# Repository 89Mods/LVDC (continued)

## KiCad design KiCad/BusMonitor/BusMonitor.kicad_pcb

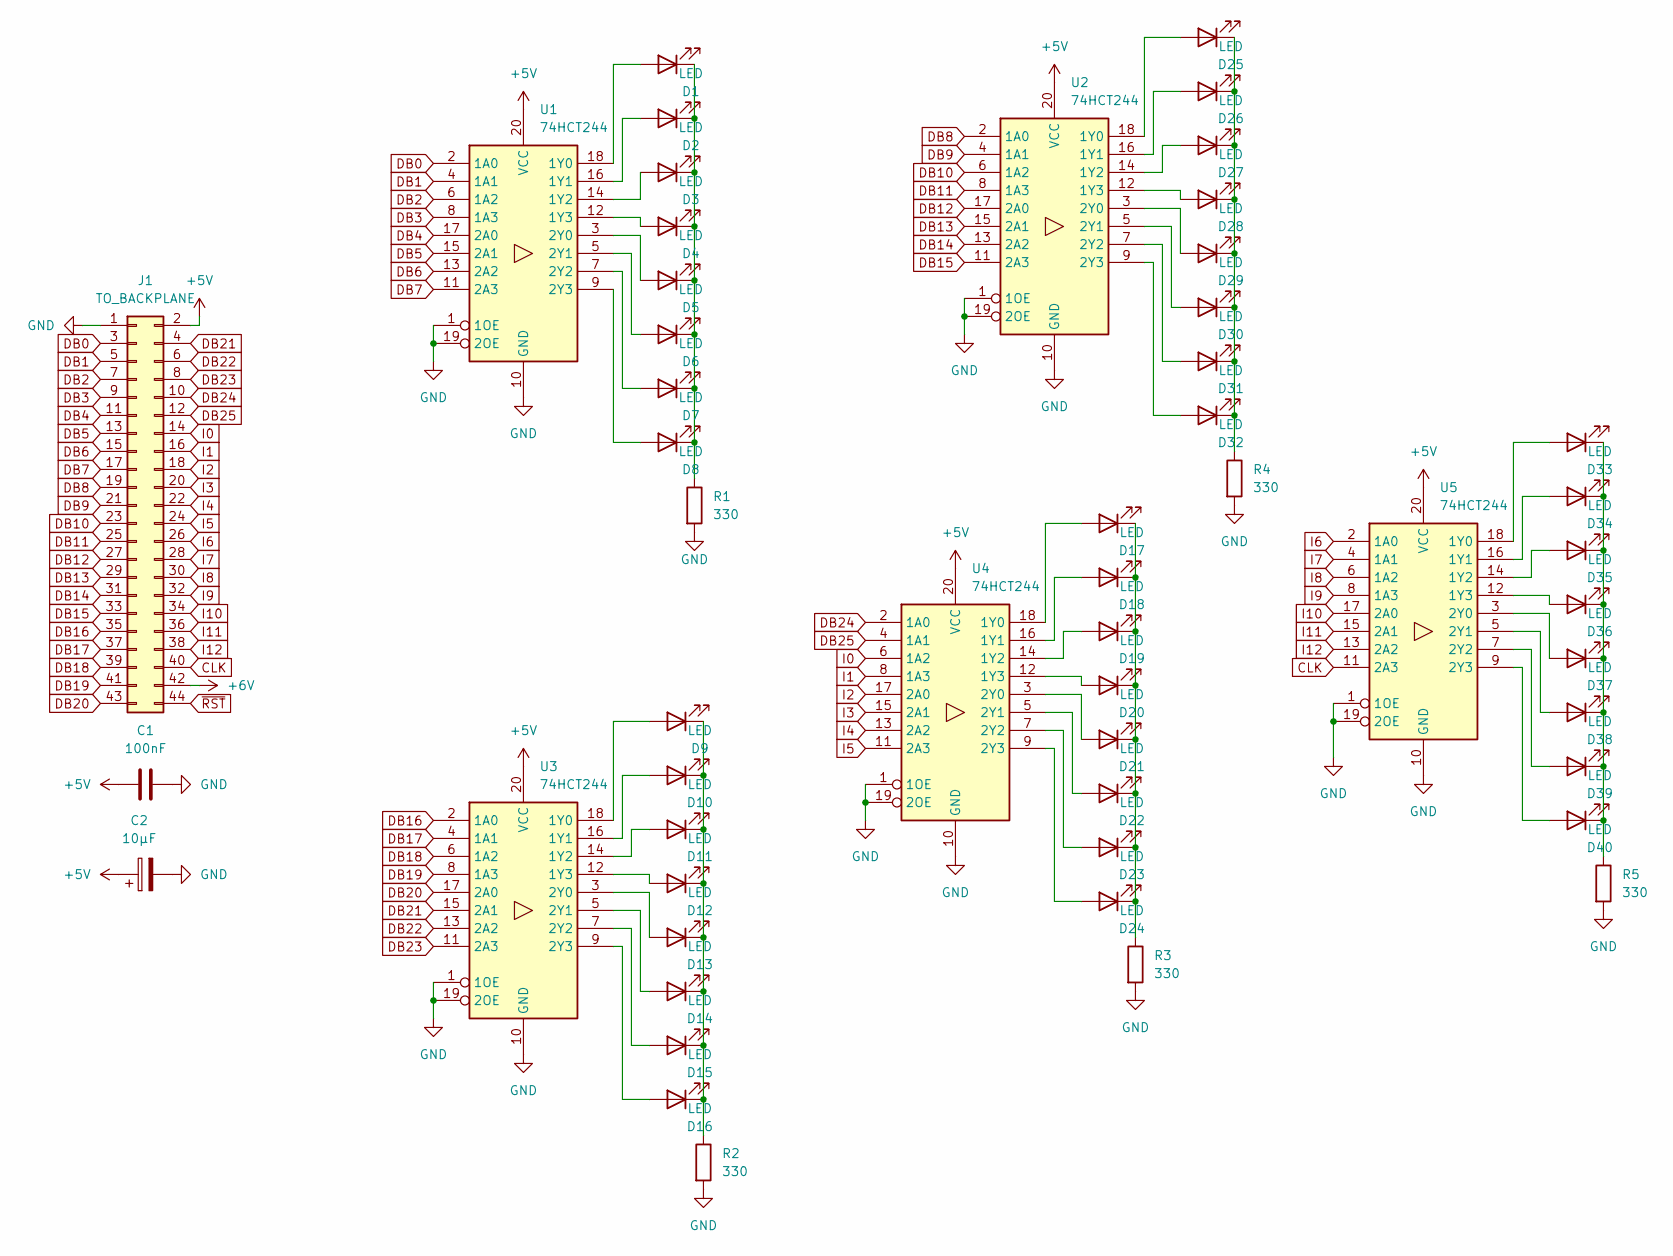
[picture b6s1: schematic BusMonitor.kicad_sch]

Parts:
C1: 100nF; C_0805_2012Metric_Pad1.18x1.45mm_HandSolder
C2: 10µF; CP_Radial_D4.0mm_P2.00mm
D1, D2, D3, D4, D5, D6, D7, D8, D9, D10, D11, D12, D13, D14, D15, D16, D17, D18, D19, D20, D21, D22, D23, D24, D25, D26, D27, D28, D29, D30, D31, D32, D33, D34, D35, D36, D37, D38, D39, D40: LED; LED_1206_3216Metric_Pad1.42x1.75mm_HandSolder
J1: TO_BACKPLANE; PinHeader_2x22_P2.54mm_Vertical
R1, R2, R3, R4, R5: 330; R_1206_3216Metric_Pad1.30x1.75mm_HandSolder
U1, U2, U3, U4, U5: 74HCT244; SO-20_12.8x7.5mm_P1.27mm

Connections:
+5V: C1.1, C2.1, J1.2, U1.20 (VCC), U2.20 (VCC), U3.20 (VCC), U4.20 (VCC), U5.20 (VCC)
+6V: J1.42
CLK: J1.40, U5.11 (2A3)
DB0: J1.3, U1.2 (1A0)
DB1: J1.5, U1.4 (1A1)
DB2: J1.7, U1.6 (1A2)
DB3: J1.9, U1.8 (1A3)
DB4: J1.11, U1.17 (2A0)
DB5: J1.13, U1.15 (2A1)
DB6: J1.15, U1.13 (2A2)
DB7: J1.17, U1.11 (2A3)
DB8: J1.19, U2.2 (1A0)
DB9: J1.21, U2.4 (1A1)
DB10: J1.23, U2.6 (1A2)
DB11: J1.25, U2.8 (1A3)
DB12: J1.27, U2.17 (2A0)
DB13: J1.29, U2.15 (2A1)
DB14: J1.31, U2.13 (2A2)
DB15: J1.33, U2.11 (2A3)
DB16: J1.35, U3.2 (1A0)
DB17: J1.37, U3.4 (1A1)
DB18: J1.39, U3.6 (1A2)
DB19: J1.41, U3.8 (1A3)
DB20: J1.43, U3.17 (2A0)
DB21: J1.4, U3.15 (2A1)
DB22: J1.6, U3.13 (2A2)
DB23: J1.8, U3.11 (2A3)
DB24: J1.10, U4.2 (1A0)
DB25: J1.12, U4.4 (1A1)
GND: C1.2, C2.2, J1.1, R1.2, R2.2, R3.2, R4.2, R5.2, U1.1 (1OE), U1.10 (GND), U1.19 (2OE), U2.1 (1OE), U2.10 (GND), U2.19 (2OE), U3.1 (1OE), U3.10 (GND), U3.19 (2OE), U4.1 (1OE), U4.10 (GND), U4.19 (2OE), U5.1 (1OE), U5.10 (GND), U5.19 (2OE)
I0: J1.14, U4.6 (1A2)
I1: J1.16, U4.8 (1A3)
I2: J1.18, U4.17 (2A0)
I3: J1.20, U4.15 (2A1)
I4: J1.22, U4.13 (2A2)
I5: J1.24, U4.11 (2A3)
I6: J1.26, U5.2 (1A0)
I7: J1.28, U5.4 (1A1)
I8: J1.30, U5.6 (1A2)
I9: J1.32, U5.8 (1A3)
I10: J1.34, U5.17 (2A0)
I11: J1.36, U5.15 (2A1)
I12: J1.38, U5.13 (2A2)
unnamed: D1.2 (A), U1.18 (1Y0)
unnamed: D1.1 (K), D2.1 (K), D3.1 (K), D4.1 (K), D5.1 (K), D6.1 (K), D7.1 (K), D8.1 (K), R1.1
unnamed: D2.2 (A), U1.16 (1Y1)
unnamed: D3.2 (A), U1.14 (1Y2)
unnamed: D4.2 (A), U1.12 (1Y3)
unnamed: D5.2 (A), U1.3 (2Y0)
unnamed: D6.2 (A), U1.5 (2Y1)
unnamed: D7.2 (A), U1.7 (2Y2)
unnamed: D8.2 (A), U1.9 (2Y3)
unnamed: D9.2 (A), U3.18 (1Y0)
unnamed: D10.2 (A), U3.16 (1Y1)
unnamed: D9.1 (K), D10.1 (K), D11.1 (K), D12.1 (K), D13.1 (K), D14.1 (K), D15.1 (K), D16.1 (K), R2.1
unnamed: D11.2 (A), U3.14 (1Y2)
unnamed: D12.2 (A), U3.12 (1Y3)
unnamed: D13.2 (A), U3.3 (2Y0)
unnamed: D14.2 (A), U3.5 (2Y1)
unnamed: D15.2 (A), U3.7 (2Y2)
unnamed: D16.2 (A), U3.9 (2Y3)
unnamed: D17.2 (A), U4.18 (1Y0)
unnamed: D17.1 (K), D18.1 (K), D19.1 (K), D20.1 (K), D21.1 (K), D22.1 (K), D23.1 (K), D24.1 (K), R3.1
unnamed: D18.2 (A), U4.16 (1Y1)
unnamed: D19.2 (A), U4.14 (1Y2)
unnamed: D20.2 (A), U4.12 (1Y3)
unnamed: D21.2 (A), U4.3 (2Y0)
unnamed: D22.2 (A), U4.5 (2Y1)
unnamed: D23.2 (A), U4.7 (2Y2)
unnamed: D24.2 (A), U4.9 (2Y3)
unnamed: D25.2 (A), U2.18 (1Y0)
unnamed: D25.1 (K), D26.1 (K), D27.1 (K), D28.1 (K), D29.1 (K), D30.1 (K), D31.1 (K), D32.1 (K), R4.1
unnamed: D26.2 (A), U2.16 (1Y1)
unnamed: D27.2 (A), U2.14 (1Y2)
unnamed: D28.2 (A), U2.12 (1Y3)
unnamed: D29.2 (A), U2.3 (2Y0)
unnamed: D30.2 (A), U2.5 (2Y1)
unnamed: D31.2 (A), U2.7 (2Y2)
unnamed: D32.2 (A), U2.9 (2Y3)
unnamed: D33.2 (A), U5.18 (1Y0)
unnamed: D33.1 (K), D34.1 (K), D35.1 (K), D36.1 (K), D37.1 (K), D38.1 (K), D39.1 (K), D40.1 (K), R5.1
unnamed: D34.2 (A), U5.16 (1Y1)
unnamed: D35.2 (A), U5.14 (1Y2)
unnamed: D36.2 (A), U5.12 (1Y3)
unnamed: D37.2 (A), U5.3 (2Y0)
unnamed: D38.2 (A), U5.5 (2Y1)
unnamed: D39.2 (A), U5.7 (2Y2)
unnamed: D40.2 (A), U5.9 (2Y3)
~RST: J1.44

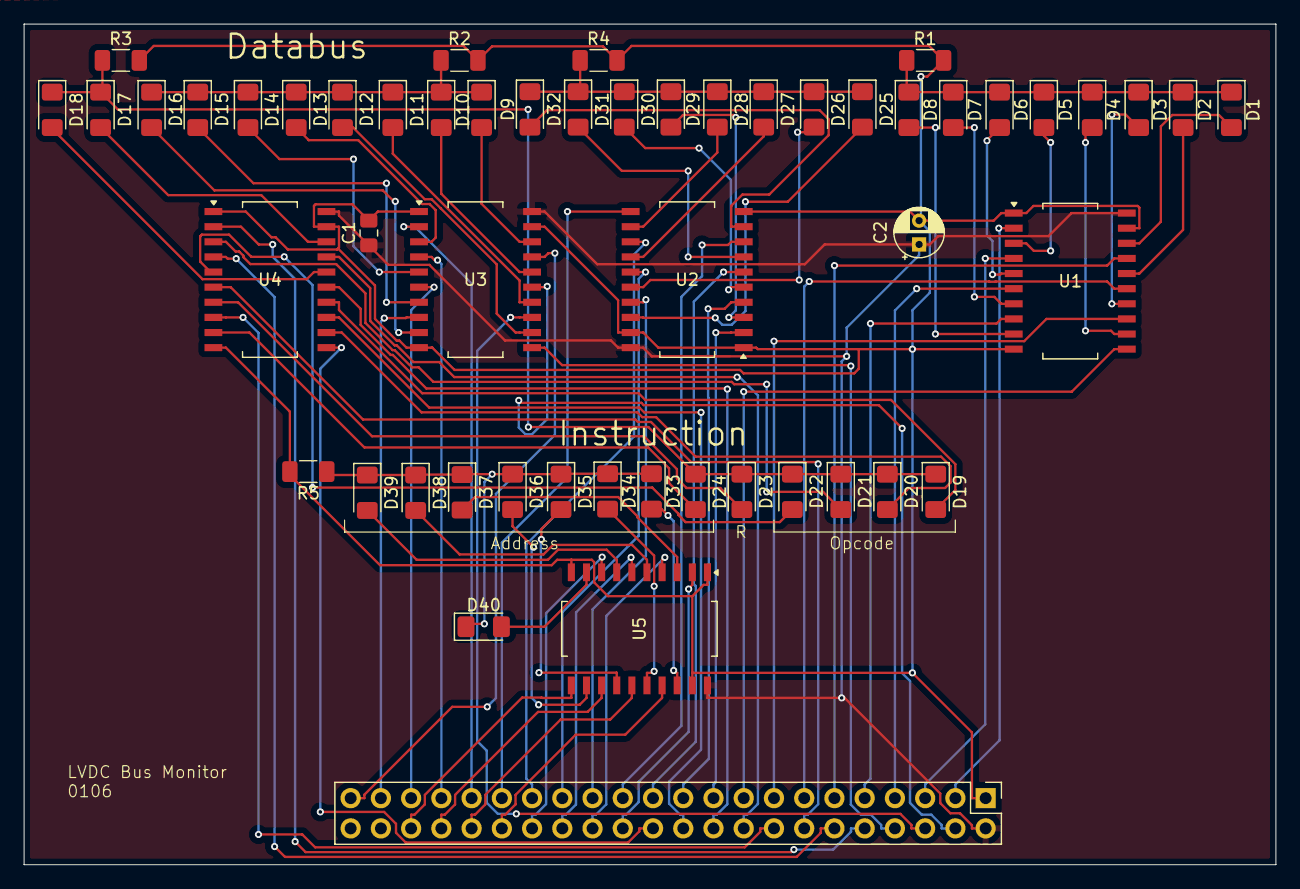
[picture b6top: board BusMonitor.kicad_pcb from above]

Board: 2 copper layers, 105.2 x 70.6 mm, 53 parts (0 on the bottom side), 87 nets.

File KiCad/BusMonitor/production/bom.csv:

Designator,Footprint,Quantity,Value,LCSC Part #
C1,0805,1,100nF,
C2,CP_Radial_D4.0mm_P2.00mm,1,10µF,
"D1, D10, D11, D12, D13, D14, D15, D16, D17, D18, D19, D2, D20, D21, D22, D23, D24, D25, D26, D27, D28, D29, D3, D30, D31, D32, D33, D34, D35, D36, D37, D38, D39, D4, D40, D5, D6, D7, D8, D9",1206,40,LED,
J1,PinHeader_2x22_P2.54mm_Vertical,1,TO_BACKPLANE,
"R1, R2, R3, R4, R5",1206,5,330,
"U1, U2, U3, U4, U5",SO-20_12.8x7.5mm_P1.27mm,5,74HCT244,

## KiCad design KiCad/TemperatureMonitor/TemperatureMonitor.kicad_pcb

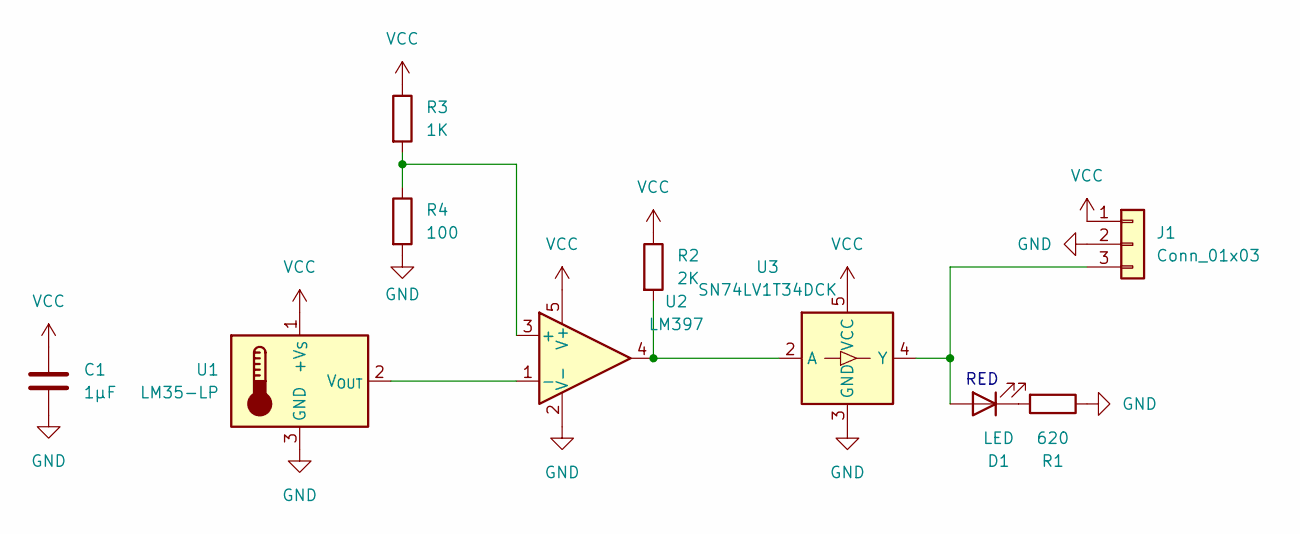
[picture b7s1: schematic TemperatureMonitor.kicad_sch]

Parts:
C1: 1µF; C_0805_2012Metric_Pad1.18x1.45mm_HandSolder
D1: LED; LED_1206_3216Metric_Pad1.42x1.75mm_HandSolder
J1: Conn_01x03; PinHeader_1x03_P2.54mm_Vertical
R1: 620; R_1206_3216Metric_Pad1.30x1.75mm_HandSolder
R2: 2K; R_1206_3216Metric_Pad1.30x1.75mm_HandSolder
R3: 1K; R_1206_3216Metric_Pad1.30x1.75mm_HandSolder
R4: 100; R_1206_3216Metric_Pad1.30x1.75mm_HandSolder
U1: LM35-LP; TO-92_Inline
U2: LM397; SOT-23-5
U3: SN74LV1T34DCK; SOT-23-5

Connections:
GND: C1.1, J1.2, R1.1, R4.2, U1.3 (GND), U2.2 (V-), U3.3 (GND)
unnamed: D1.2 (A), J1.3, U3.4 (Y)
unnamed: D1.1 (K), R1.2
unnamed: U1.2 (V_{OUT}), U2.1 (-)
unnamed: R3.2, R4.1, U2.3 (+)
unnamed: R2.2, U2.4, U3.2 (A)
VCC: C1.2, J1.1, R2.1, R3.1, U1.1 (+V_{S}), U2.5 (V+), U3.5 (VCC)

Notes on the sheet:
RED

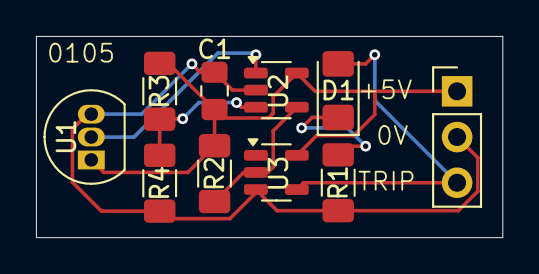
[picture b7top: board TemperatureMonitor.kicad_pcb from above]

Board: 2 copper layers, 25.9 x 11.2 mm, 10 parts (0 on the bottom side), 7 nets.

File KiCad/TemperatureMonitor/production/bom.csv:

Designator,Footprint,Quantity,Value,LCSC Part #
C1,0805,1,1µF,
D1,1206,1,LED,
J1,PinHeader_1x03_P2.54mm_Vertical,1,Conn_01x03,
R1,1206,1,620,
R2,1206,1,2K,
R3,1206,1,1K,
R4,1206,1,4.7K,
U1,TO-92_Inline,1,LM35-LP,
U2,SOT-23-5,1,LM397,
U3,SOT-23-5,1,SN74LV1T34DCK,

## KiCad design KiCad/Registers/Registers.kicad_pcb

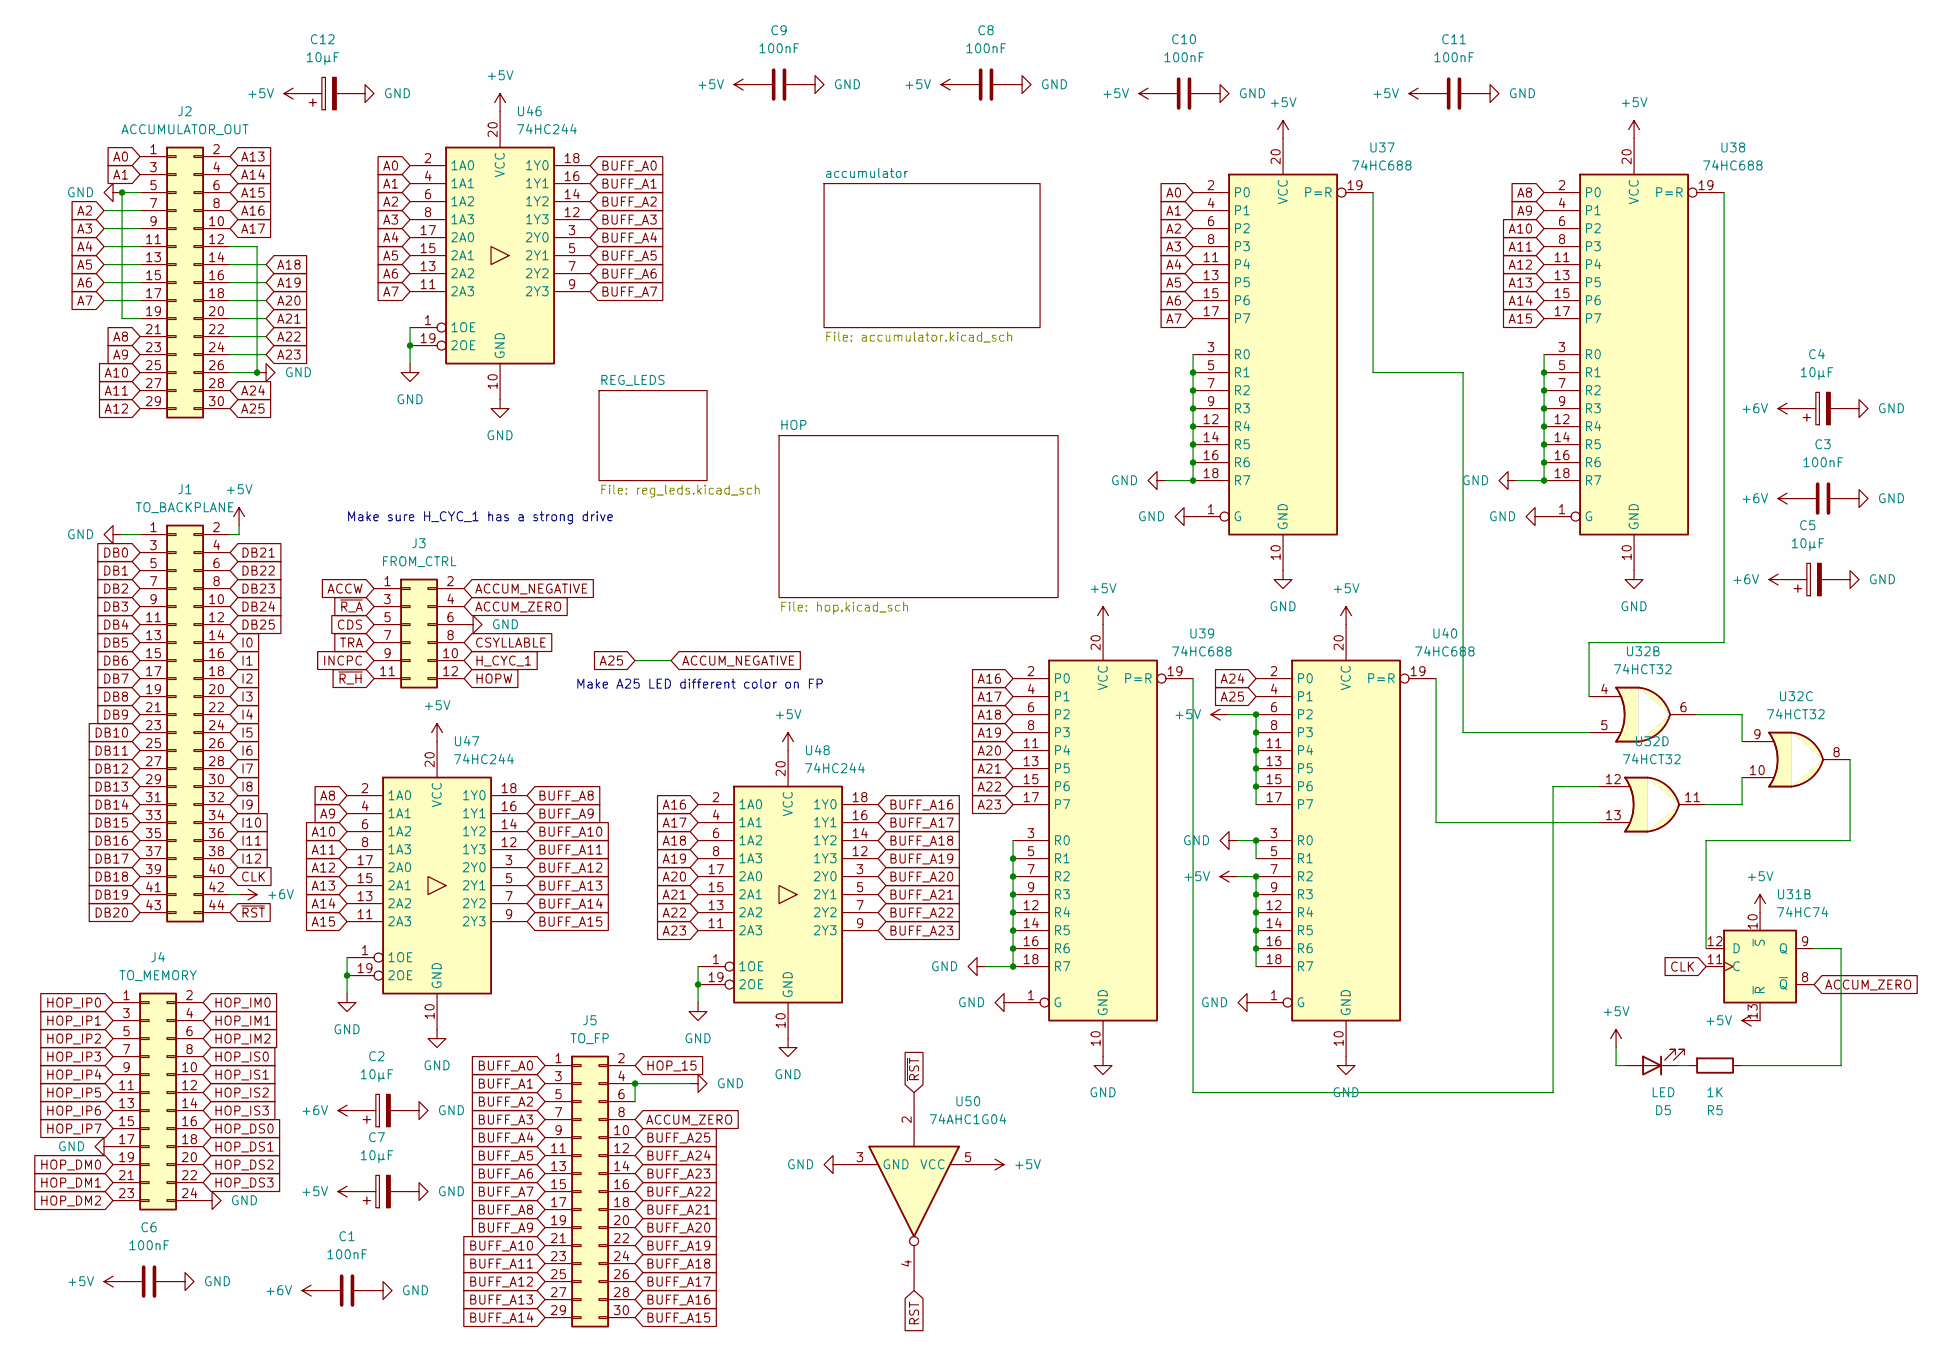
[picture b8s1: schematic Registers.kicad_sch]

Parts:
C1, C3, C6, C8, C9, C10, C11: 100nF; C_0805_2012Metric_Pad1.18x1.45mm_HandSolder
C2, C4, C5, C7, C12: 10µF; CP_Radial_D4.0mm_P2.00mm
D5: LED; LED_1206_3216Metric_Pad1.42x1.75mm_HandSolder
J1: TO_BACKPLANE; PinHeader_2x22_P2.54mm_Vertical
J2: ACCUMULATOR_OUT; PinHeader_2x15_P2.54mm_Vertical
J3: FROM_CTRL; PinHeader_2x06_P2.54mm_Vertical
J4: TO_MEMORY; PinHeader_2x12_P2.54mm_Vertical
J5: TO_FP; PinHeader_2x15_P2.54mm_Vertical
R5: 1K; R_1206_3216Metric_Pad1.30x1.75mm_HandSolder
U31: 74HC74; SO-14_3.9x8.65mm_P1.27mm
U32: 74HCT32; SO-14_3.9x8.65mm_P1.27mm
U37, U38, U39, U40: 74HC688; SO-20_12.8x7.5mm_P1.27mm
U46, U47, U48: 74HC244; SO-20_12.8x7.5mm_P1.27mm
U50: 74AHC1G04; SOIC-6

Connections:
+5V: C6.1, C7.1, C8.1, C9.1, C10.1, C11.1, C12.1, D5.2 (A), J1.2, U31.10 (~S), U31.13 (~R), U37.20 (VCC), U38.20 (VCC), U39.20 (VCC), U40.6 (P2), U40.7 (R2), U40.8 (P3), U40.9 (R3), U40.11 (P4), U40.12 (R4), U40.13 (P5), U40.14 (R5), U40.15 (P6), U40.16 (R6), U40.17 (P7), U40.18 (R7), U40.20 (VCC), U46.20 (VCC), U47.20 (VCC), U48.20 (VCC), U50.5 (VCC); also elsewhere on the board
+6V: C1.1, C2.1, C3.1, C4.1, C5.1, J1.42; also elsewhere on the board
A0: J2.1, U37.2 (P0), U46.2 (1A0); also elsewhere on the board
A1: J2.3, U37.4 (P1), U46.4 (1A1); also elsewhere on the board
A2: J2.7, U37.6 (P2), U46.6 (1A2); also elsewhere on the board
A3: J2.9, U37.8 (P3), U46.8 (1A3); also elsewhere on the board
A4: J2.11, U37.11 (P4), U46.17 (2A0); also elsewhere on the board
A5: J2.13, U37.13 (P5), U46.15 (2A1); also elsewhere on the board
A6: J2.15, U37.15 (P6), U46.13 (2A2); also elsewhere on the board
A7: J2.17, U37.17 (P7), U46.11 (2A3); also elsewhere on the board
A8: J2.21, U38.2 (P0), U47.2 (1A0); also elsewhere on the board
A9: J2.23, U38.4 (P1), U47.4 (1A1); also elsewhere on the board
A10: J2.25, U38.6 (P2), U47.6 (1A2); also elsewhere on the board
A11: J2.27, U38.8 (P3), U47.8 (1A3); also elsewhere on the board
A12: J2.29, U38.11 (P4), U47.17 (2A0); also elsewhere on the board
A13: J2.2, U38.13 (P5), U47.15 (2A1); also elsewhere on the board
A14: J2.4, U38.15 (P6), U47.13 (2A2); also elsewhere on the board
A15: J2.6, U38.17 (P7), U47.11 (2A3); also elsewhere on the board
A16: J2.8, U39.2 (P0), U48.2 (1A0); also elsewhere on the board
A17: J2.10, U39.4 (P1), U48.4 (1A1); also elsewhere on the board
A18: J2.14, U39.6 (P2), U48.6 (1A2); also elsewhere on the board
A19: J2.16, U39.8 (P3), U48.8 (1A3); also elsewhere on the board
A20: J2.18, U39.11 (P4), U48.17 (2A0); also elsewhere on the board
A21: J2.20, U39.13 (P5), U48.15 (2A1); also elsewhere on the board
A22: J2.22, U39.15 (P6), U48.13 (2A2); also elsewhere on the board
A23: J2.24, U39.17 (P7), U48.11 (2A3); also elsewhere on the board
A24: J2.28, U40.2 (P0); also elsewhere on the board
A25: J2.30, J3.2, U40.4 (P1); also elsewhere on the board
ACCUM_ZERO: J3.4, J5.8, U31.8 (~Q)
ACCW: J3.1; also elsewhere on the board
BUFF_A0: J5.1, U46.18 (1Y0)
BUFF_A1: J5.3, U46.16 (1Y1)
BUFF_A2: J5.5, U46.14 (1Y2)
BUFF_A3: J5.7, U46.12 (1Y3)
BUFF_A4: J5.9, U46.3 (2Y0)
BUFF_A5: J5.11, U46.5 (2Y1)
BUFF_A6: J5.13, U46.7 (2Y2)
BUFF_A7: J5.15, U46.9 (2Y3)
BUFF_A8: J5.17, U47.18 (1Y0)
BUFF_A9: J5.19, U47.16 (1Y1)
BUFF_A10: J5.21, U47.14 (1Y2)
BUFF_A11: J5.23, U47.12 (1Y3)
BUFF_A12: J5.25, U47.3 (2Y0)
BUFF_A13: J5.27, U47.5 (2Y1)
BUFF_A14: J5.29, U47.7 (2Y2)
BUFF_A15: J5.30, U47.9 (2Y3)
BUFF_A16: J5.28, U48.18 (1Y0)
BUFF_A17: J5.26, U48.16 (1Y1)
BUFF_A18: J5.24, U48.14 (1Y2)
BUFF_A19: J5.22, U48.12 (1Y3)
BUFF_A20: J5.20, U48.3 (2Y0)
BUFF_A21: J5.18, U48.5 (2Y1)
BUFF_A22: J5.16, U48.7 (2Y2)
BUFF_A23: J5.14, U48.9 (2Y3)
BUFF_A24: J5.12; also elsewhere on the board
BUFF_A25: J5.10; also elsewhere on the board
CDS: J3.5; also elsewhere on the board
CLK: J1.40, U31.11 (C); also elsewhere on the board
CSYLLABLE: J3.8; also elsewhere on the board
DB0: J1.3; also elsewhere on the board
DB1: J1.5; also elsewhere on the board
DB2: J1.7; also elsewhere on the board
DB3: J1.9; also elsewhere on the board
DB4: J1.11; also elsewhere on the board
DB5: J1.13; also elsewhere on the board
DB6: J1.15; also elsewhere on the board
DB7: J1.17; also elsewhere on the board
DB8: J1.19; also elsewhere on the board
DB9: J1.21; also elsewhere on the board
DB10: J1.23; also elsewhere on the board
DB11: J1.25; also elsewhere on the board
DB12: J1.27; also elsewhere on the board
DB13: J1.29; also elsewhere on the board
DB14: J1.31; also elsewhere on the board
DB15: J1.33; also elsewhere on the board
DB16: J1.35; also elsewhere on the board
DB17: J1.37; also elsewhere on the board
DB18: J1.39; also elsewhere on the board
DB19: J1.41; also elsewhere on the board
DB20: J1.43; also elsewhere on the board
DB21: J1.4; also elsewhere on the board
DB22: J1.6; also elsewhere on the board
DB23: J1.8; also elsewhere on the board
DB24: J1.10; also elsewhere on the board
DB25: J1.12; also elsewhere on the board
GND: C1.2, C2.2, C3.2, C4.2, C5.2, C6.2, C7.2, C8.2, C9.2, C10.2, C11.2, C12.2, J1.1, J2.5, J2.12, J2.19, J2.26, J3.6, J4.17, J4.24, J5.4, J5.6, U37.1 (G), U37.3 (R0), U37.5 (R1), U37.7 (R2), U37.9 (R3), U37.10 (GND), U37.12 (R4), U37.14 (R5), U37.16 (R6), U37.18 (R7), U38.1 (G), U38.3 (R0), U38.5 (R1), U38.7 (R2), U38.9 (R3), U38.10 (GND), U38.12 (R4), U38.14 (R5), U38.16 (R6), U38.18 (R7), U39.1 (G), U39.3 (R0), U39.5 (R1), U39.7 (R2), U39.9 (R3), U39.10 (GND), U39.12 (R4), U39.14 (R5), U39.16 (R6), U39.18 (R7), U40.1 (G), U40.3 (R0), U40.5 (R1), U40.10 (GND), U46.1 (1OE), U46.10 (GND), U46.19 (2OE), U47.1 (1OE), U47.10 (GND), U47.19 (2OE), U48.1 (1OE), U48.10 (GND), U48.19 (2OE), U50.3 (GND); also elsewhere on the board
HOPW: J3.12; also elsewhere on the board
HOP_15: J5.2; also elsewhere on the board
HOP_DM0: J4.19; also elsewhere on the board
HOP_DM1: J4.21; also elsewhere on the board
HOP_DM2: J4.23; also elsewhere on the board
HOP_DS0: J4.16; also elsewhere on the board
HOP_DS1: J4.18; also elsewhere on the board
HOP_DS2: J4.20; also elsewhere on the board
HOP_DS3: J4.22; also elsewhere on the board
HOP_IM0: J4.2; also elsewhere on the board
HOP_IM1: J4.4; also elsewhere on the board
HOP_IM2: J4.6; also elsewhere on the board
HOP_IP0: J4.1; also elsewhere on the board
HOP_IP1: J4.3; also elsewhere on the board
HOP_IP2: J4.5; also elsewhere on the board
HOP_IP3: J4.7; also elsewhere on the board
HOP_IP4: J4.9; also elsewhere on the board
HOP_IP5: J4.11; also elsewhere on the board
HOP_IP6: J4.13; also elsewhere on the board
HOP_IP7: J4.15; also elsewhere on the board
HOP_IS0: J4.8; also elsewhere on the board
HOP_IS1: J4.10; also elsewhere on the board
HOP_IS2: J4.12; also elsewhere on the board
HOP_IS3: J4.14; also elsewhere on the board
H_CYC_1: J3.10; also elsewhere on the board
I0: J1.14
I1: J1.16
I2: J1.18
I3: J1.20
I4: J1.22; also elsewhere on the board
I5: J1.24; also elsewhere on the board
I6: J1.26; also elsewhere on the board
I7: J1.28; also elsewhere on the board
I8: J1.30; also elsewhere on the board
I9: J1.32; also elsewhere on the board
I10: J1.34; also elsewhere on the board
I11: J1.36; also elsewhere on the board
I12: J1.38; also elsewhere on the board
INCPC: J3.9; also elsewhere on the board
unnamed: D5.1 (K), R5.2
unnamed: U31.12 (D), U32.8
unnamed: R5.1, U31.9 (Q)
unnamed: U32.6, U32.9
unnamed: U32.10, U32.11
unnamed: U32.5, U37.19 (P=R)
unnamed: U32.4, U38.19 (P=R)
unnamed: U32.12, U39.19 (P=R)
unnamed: U32.13, U40.19 (P=R)
RST: U50.4; also elsewhere on the board
TRA: J3.7; also elsewhere on the board
~RST: J1.44, U50.2; also elsewhere on the board
~R_A: J3.3; also elsewhere on the board
~R_H: J3.11; also elsewhere on the board

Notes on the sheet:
Make A25 LED different color on FP
Make sure H_CYC_1 has a strong drive

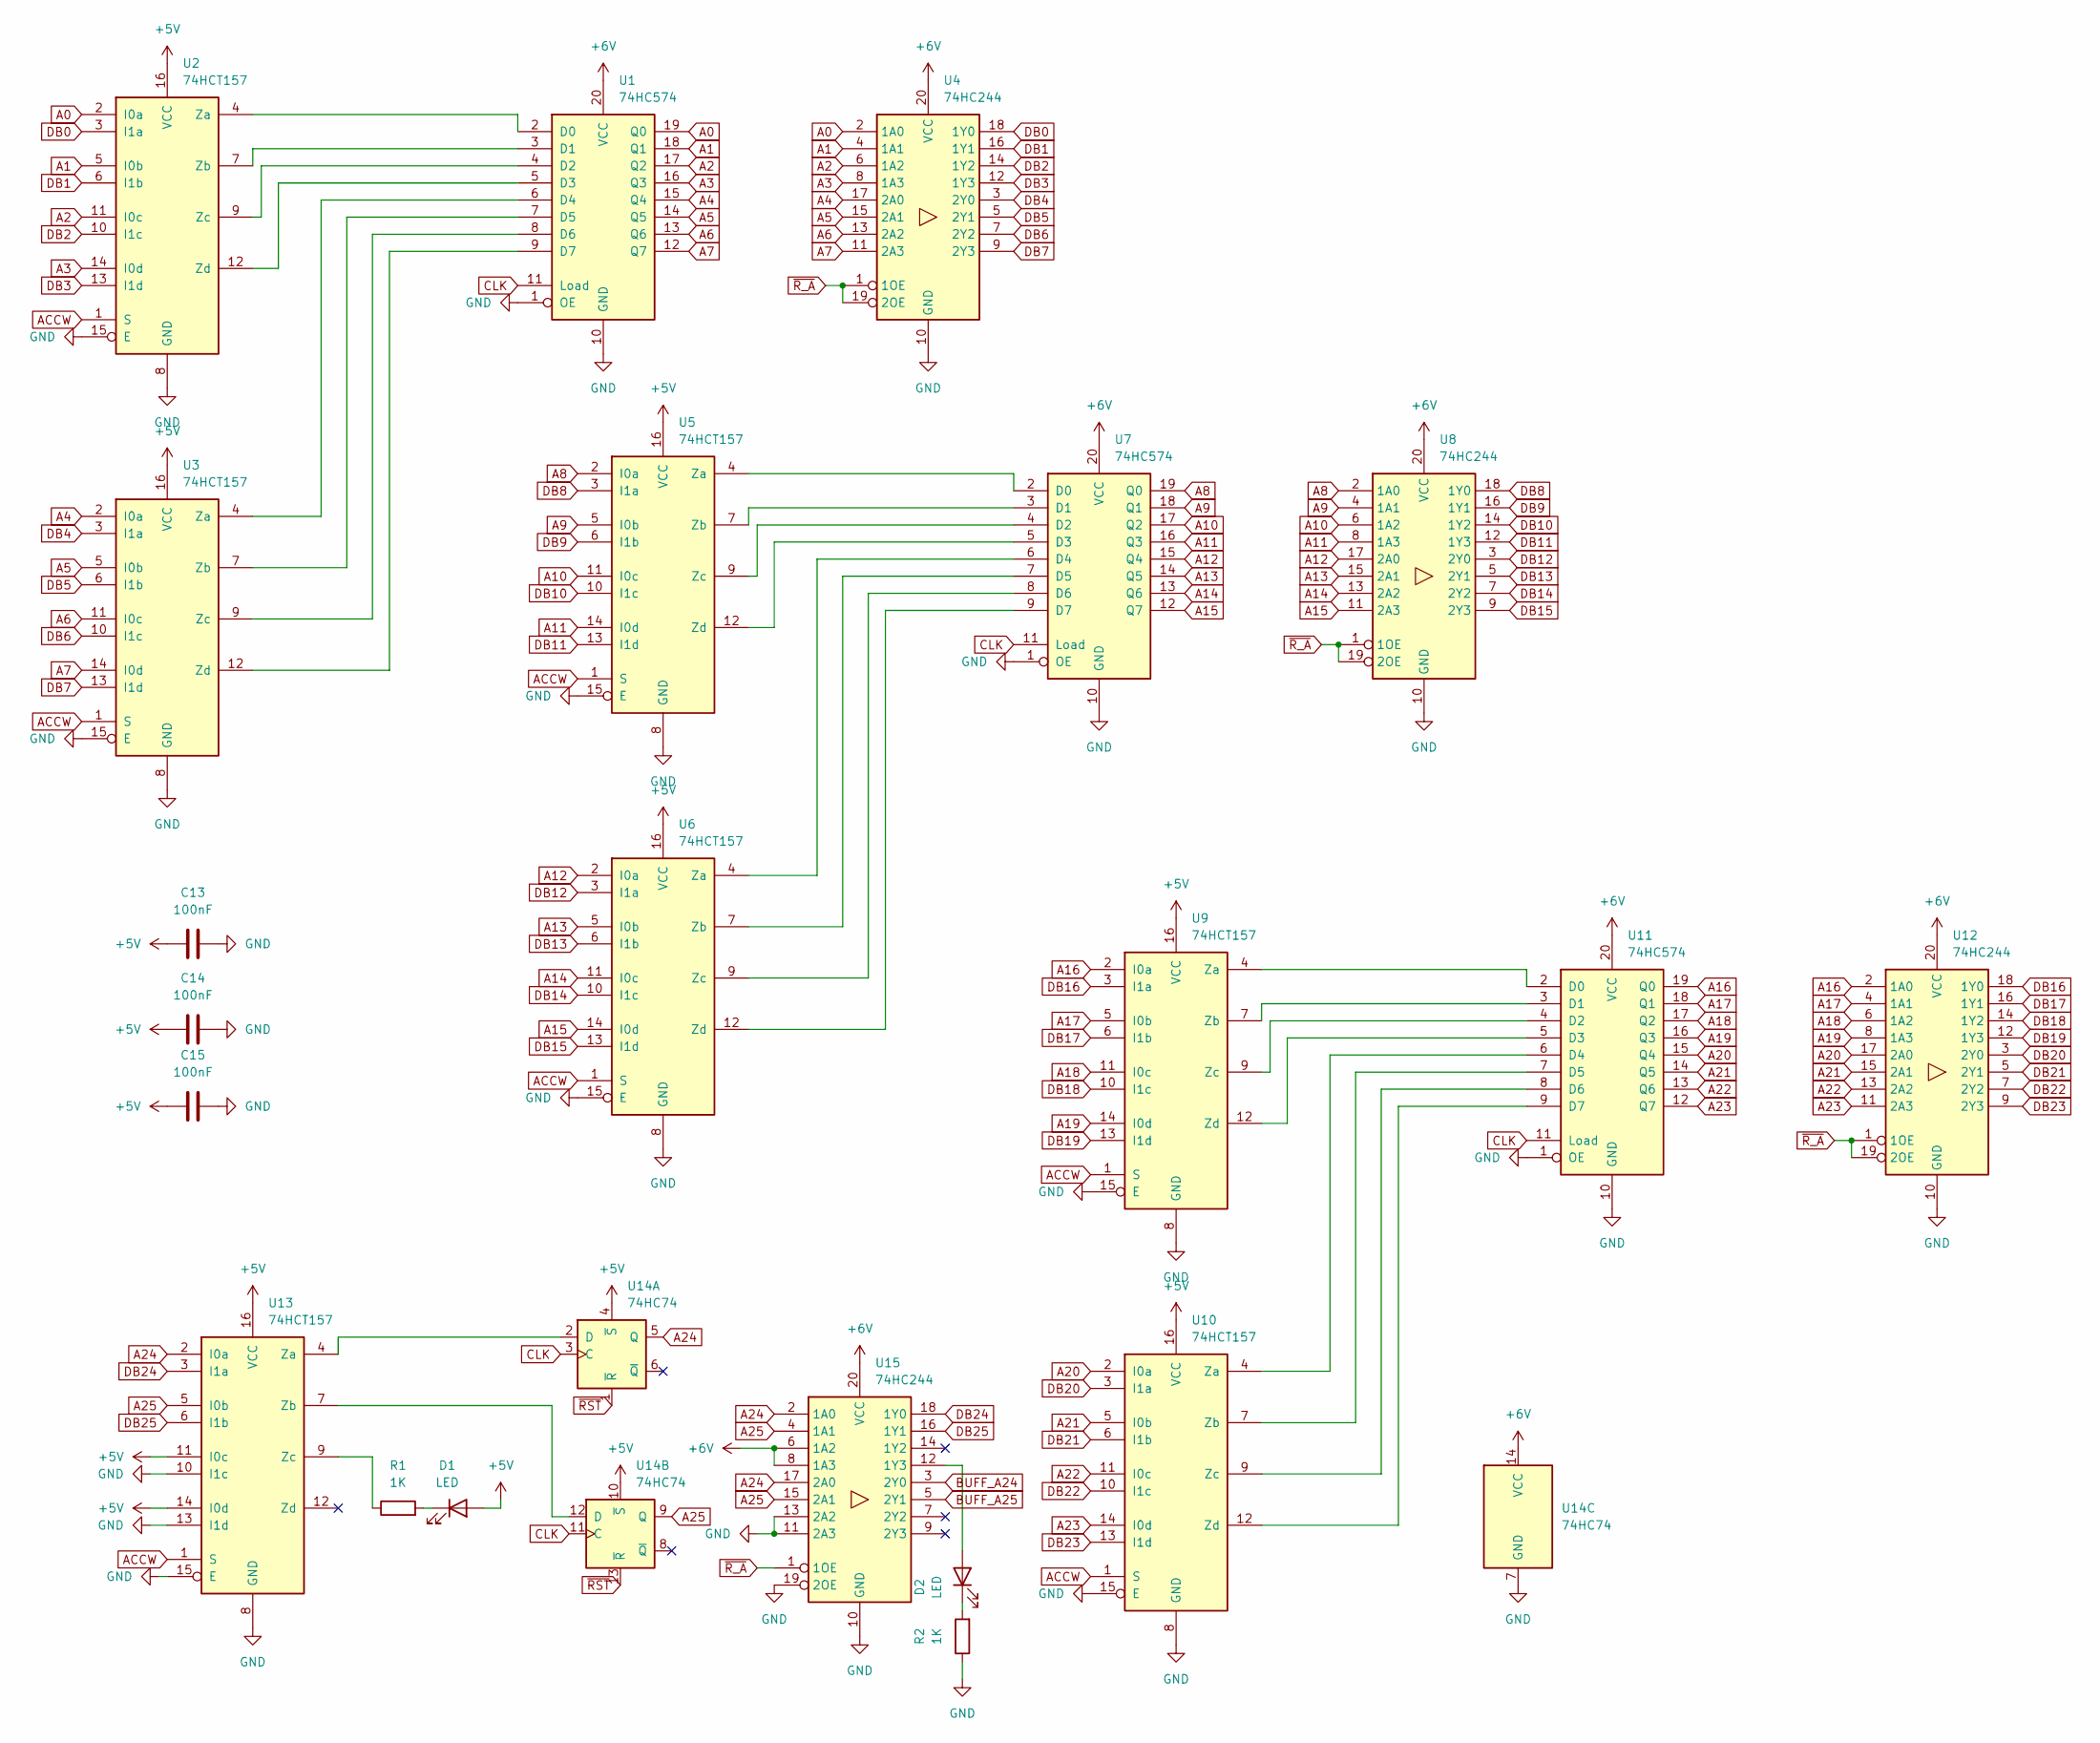
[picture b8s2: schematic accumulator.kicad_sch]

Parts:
C13, C14, C15: 100nF; C_0805_2012Metric_Pad1.18x1.45mm_HandSolder
D1, D2: LED; LED_1206_3216Metric_Pad1.42x1.75mm_HandSolder
R1, R2: 1K; R_1206_3216Metric_Pad1.30x1.75mm_HandSolder
U1, U7, U11: 74HC574; SO-20_12.8x7.5mm_P1.27mm
U2, U3, U5, U6, U9, U10, U13: 74HCT157; SO-16_3.9x9.9mm_P1.27mm
U4, U8, U12, U15: 74HC244; SO-20_12.8x7.5mm_P1.27mm
U14: 74HC74; SO-14_3.9x8.65mm_P1.27mm

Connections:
+5V: C13.1, C14.1, C15.1, D1.2 (A), U2.16 (VCC), U3.16 (VCC), U5.16 (VCC), U6.16 (VCC), U9.16 (VCC), U10.16 (VCC), U13.11 (I0c), U13.14 (I0d), U13.16 (VCC), U14.4 (~S), U14.10 (~S); also elsewhere on the board
+6V: U1.20 (VCC), U4.20 (VCC), U7.20 (VCC), U8.20 (VCC), U11.20 (VCC), U12.20 (VCC), U14.14 (VCC), U15.6 (1A2), U15.8 (1A3), U15.20 (VCC); also elsewhere on the board
A0: U1.19 (Q0), U2.2 (I0a), U4.2 (1A0); also elsewhere on the board
A1: U1.18 (Q1), U2.5 (I0b), U4.4 (1A1); also elsewhere on the board
A2: U1.17 (Q2), U2.11 (I0c), U4.6 (1A2); also elsewhere on the board
A3: U1.16 (Q3), U2.14 (I0d), U4.8 (1A3); also elsewhere on the board
A4: U1.15 (Q4), U3.2 (I0a), U4.17 (2A0); also elsewhere on the board
A5: U1.14 (Q5), U3.5 (I0b), U4.15 (2A1); also elsewhere on the board
A6: U1.13 (Q6), U3.11 (I0c), U4.13 (2A2); also elsewhere on the board
A7: U1.12 (Q7), U3.14 (I0d), U4.11 (2A3); also elsewhere on the board
A8: U5.2 (I0a), U7.19 (Q0), U8.2 (1A0); also elsewhere on the board
A9: U5.5 (I0b), U7.18 (Q1), U8.4 (1A1); also elsewhere on the board
A10: U5.11 (I0c), U7.17 (Q2), U8.6 (1A2); also elsewhere on the board
A11: U5.14 (I0d), U7.16 (Q3), U8.8 (1A3); also elsewhere on the board
A12: U6.2 (I0a), U7.15 (Q4), U8.17 (2A0); also elsewhere on the board
A13: U6.5 (I0b), U7.14 (Q5), U8.15 (2A1); also elsewhere on the board
A14: U6.11 (I0c), U7.13 (Q6), U8.13 (2A2); also elsewhere on the board
A15: U6.14 (I0d), U7.12 (Q7), U8.11 (2A3); also elsewhere on the board
A16: U9.2 (I0a), U11.19 (Q0), U12.2 (1A0); also elsewhere on the board
A17: U9.5 (I0b), U11.18 (Q1), U12.4 (1A1); also elsewhere on the board
A18: U9.11 (I0c), U11.17 (Q2), U12.6 (1A2); also elsewhere on the board
A19: U9.14 (I0d), U11.16 (Q3), U12.8 (1A3); also elsewhere on the board
A20: U10.2 (I0a), U11.15 (Q4), U12.17 (2A0); also elsewhere on the board
A21: U10.5 (I0b), U11.14 (Q5), U12.15 (2A1); also elsewhere on the board
A22: U10.11 (I0c), U11.13 (Q6), U12.13 (2A2); also elsewhere on the board
A23: U10.14 (I0d), U11.12 (Q7), U12.11 (2A3); also elsewhere on the board
A24: U13.2 (I0a), U14.5 (Q), U15.2 (1A0), U15.17 (2A0); also elsewhere on the board
A25: U13.5 (I0b), U14.9 (Q), U15.4 (1A1), U15.15 (2A1); also elsewhere on the board
ACCW: U2.1 (S), U3.1 (S), U5.1 (S), U6.1 (S), U9.1 (S), U10.1 (S), U13.1 (S); also elsewhere on the board
BUFF_A24: U15.3 (2Y0); also elsewhere on the board
BUFF_A25: U15.5 (2Y1); also elsewhere on the board
CLK: U1.11 (Load), U7.11 (Load), U11.11 (Load), U14.3 (C), U14.11 (C); also elsewhere on the board
DB0: U2.3 (I1a), U4.18 (1Y0); also elsewhere on the board
DB1: U2.6 (I1b), U4.16 (1Y1); also elsewhere on the board
DB2: U2.10 (I1c), U4.14 (1Y2); also elsewhere on the board
DB3: U2.13 (I1d), U4.12 (1Y3); also elsewhere on the board
DB4: U3.3 (I1a), U4.3 (2Y0); also elsewhere on the board
DB5: U3.6 (I1b), U4.5 (2Y1); also elsewhere on the board
DB6: U3.10 (I1c), U4.7 (2Y2); also elsewhere on the board
DB7: U3.13 (I1d), U4.9 (2Y3); also elsewhere on the board
DB8: U5.3 (I1a), U8.18 (1Y0); also elsewhere on the board
DB9: U5.6 (I1b), U8.16 (1Y1); also elsewhere on the board
DB10: U5.10 (I1c), U8.14 (1Y2); also elsewhere on the board
DB11: U5.13 (I1d), U8.12 (1Y3); also elsewhere on the board
DB12: U6.3 (I1a), U8.3 (2Y0); also elsewhere on the board
DB13: U6.6 (I1b), U8.5 (2Y1); also elsewhere on the board
DB14: U6.10 (I1c), U8.7 (2Y2); also elsewhere on the board
DB15: U6.13 (I1d), U8.9 (2Y3); also elsewhere on the board
DB16: U9.3 (I1a), U12.18 (1Y0); also elsewhere on the board
DB17: U9.6 (I1b), U12.16 (1Y1); also elsewhere on the board
DB18: U9.10 (I1c), U12.14 (1Y2); also elsewhere on the board
DB19: U9.13 (I1d), U12.12 (1Y3); also elsewhere on the board
DB20: U10.3 (I1a), U12.3 (2Y0); also elsewhere on the board
DB21: U10.6 (I1b), U12.5 (2Y1); also elsewhere on the board
DB22: U10.10 (I1c), U12.7 (2Y2); also elsewhere on the board
DB23: U10.13 (I1d), U12.9 (2Y3); also elsewhere on the board
DB24: U13.3 (I1a), U15.18 (1Y0); also elsewhere on the board
DB25: U13.6 (I1b), U15.16 (1Y1); also elsewhere on the board
GND: C13.2, C14.2, C15.2, R2.1, U1.1 (OE), U1.10 (GND), U2.8 (GND), U2.15 (E), U3.8 (GND), U3.15 (E), U4.10 (GND), U5.8 (GND), U5.15 (E), U6.8 (GND), U6.15 (E), U7.1 (OE), U7.10 (GND), U8.10 (GND), U9.8 (GND), U9.15 (E), U10.8 (GND), U10.15 (E), U11.1 (OE), U11.10 (GND), U12.10 (GND), U13.8 (GND), U13.10 (I1c), U13.13 (I1d), U13.15 (E), U14.7 (GND), U15.10 (GND), U15.11 (2A3), U15.13 (2A2), U15.19 (2OE); also elsewhere on the board
unnamed: D1.1 (K), R1.2
unnamed: D2.2 (A), U15.12 (1Y3)
unnamed: D2.1 (K), R2.2
unnamed: U1.2 (D0), U2.4 (Za)
unnamed: U1.3 (D1), U2.7 (Zb)
unnamed: U1.4 (D2), U2.9 (Zc)
unnamed: U1.5 (D3), U2.12 (Zd)
unnamed: U1.6 (D4), U3.4 (Za)
unnamed: U1.7 (D5), U3.7 (Zb)
unnamed: U1.8 (D6), U3.9 (Zc)
unnamed: U1.9 (D7), U3.12 (Zd)
unnamed: U5.4 (Za), U7.2 (D0)
unnamed: U5.7 (Zb), U7.3 (D1)
unnamed: U5.9 (Zc), U7.4 (D2)
unnamed: U5.12 (Zd), U7.5 (D3)
unnamed: U6.4 (Za), U7.6 (D4)
unnamed: U6.7 (Zb), U7.7 (D5)
unnamed: U6.9 (Zc), U7.8 (D6)
unnamed: U6.12 (Zd), U7.9 (D7)
unnamed: U10.4 (Za), U11.6 (D4)
unnamed: U10.7 (Zb), U11.7 (D5)
unnamed: U10.9 (Zc), U11.8 (D6)
unnamed: U10.12 (Zd), U11.9 (D7)
unnamed: U9.4 (Za), U11.2 (D0)
unnamed: U9.7 (Zb), U11.3 (D1)
unnamed: U9.9 (Zc), U11.4 (D2)
unnamed: U9.12 (Zd), U11.5 (D3)
unnamed: U13.4 (Za), U14.2 (D)
unnamed: U13.7 (Zb), U14.12 (D)
unnamed: R1.1, U13.9 (Zc)
~RST: U14.1 (~R), U14.13 (~R); also elsewhere on the board
~R_A: U4.1 (1OE), U4.19 (2OE), U8.1 (1OE), U8.19 (2OE), U12.1 (1OE), U12.19 (2OE), U15.1 (1OE); also elsewhere on the board
